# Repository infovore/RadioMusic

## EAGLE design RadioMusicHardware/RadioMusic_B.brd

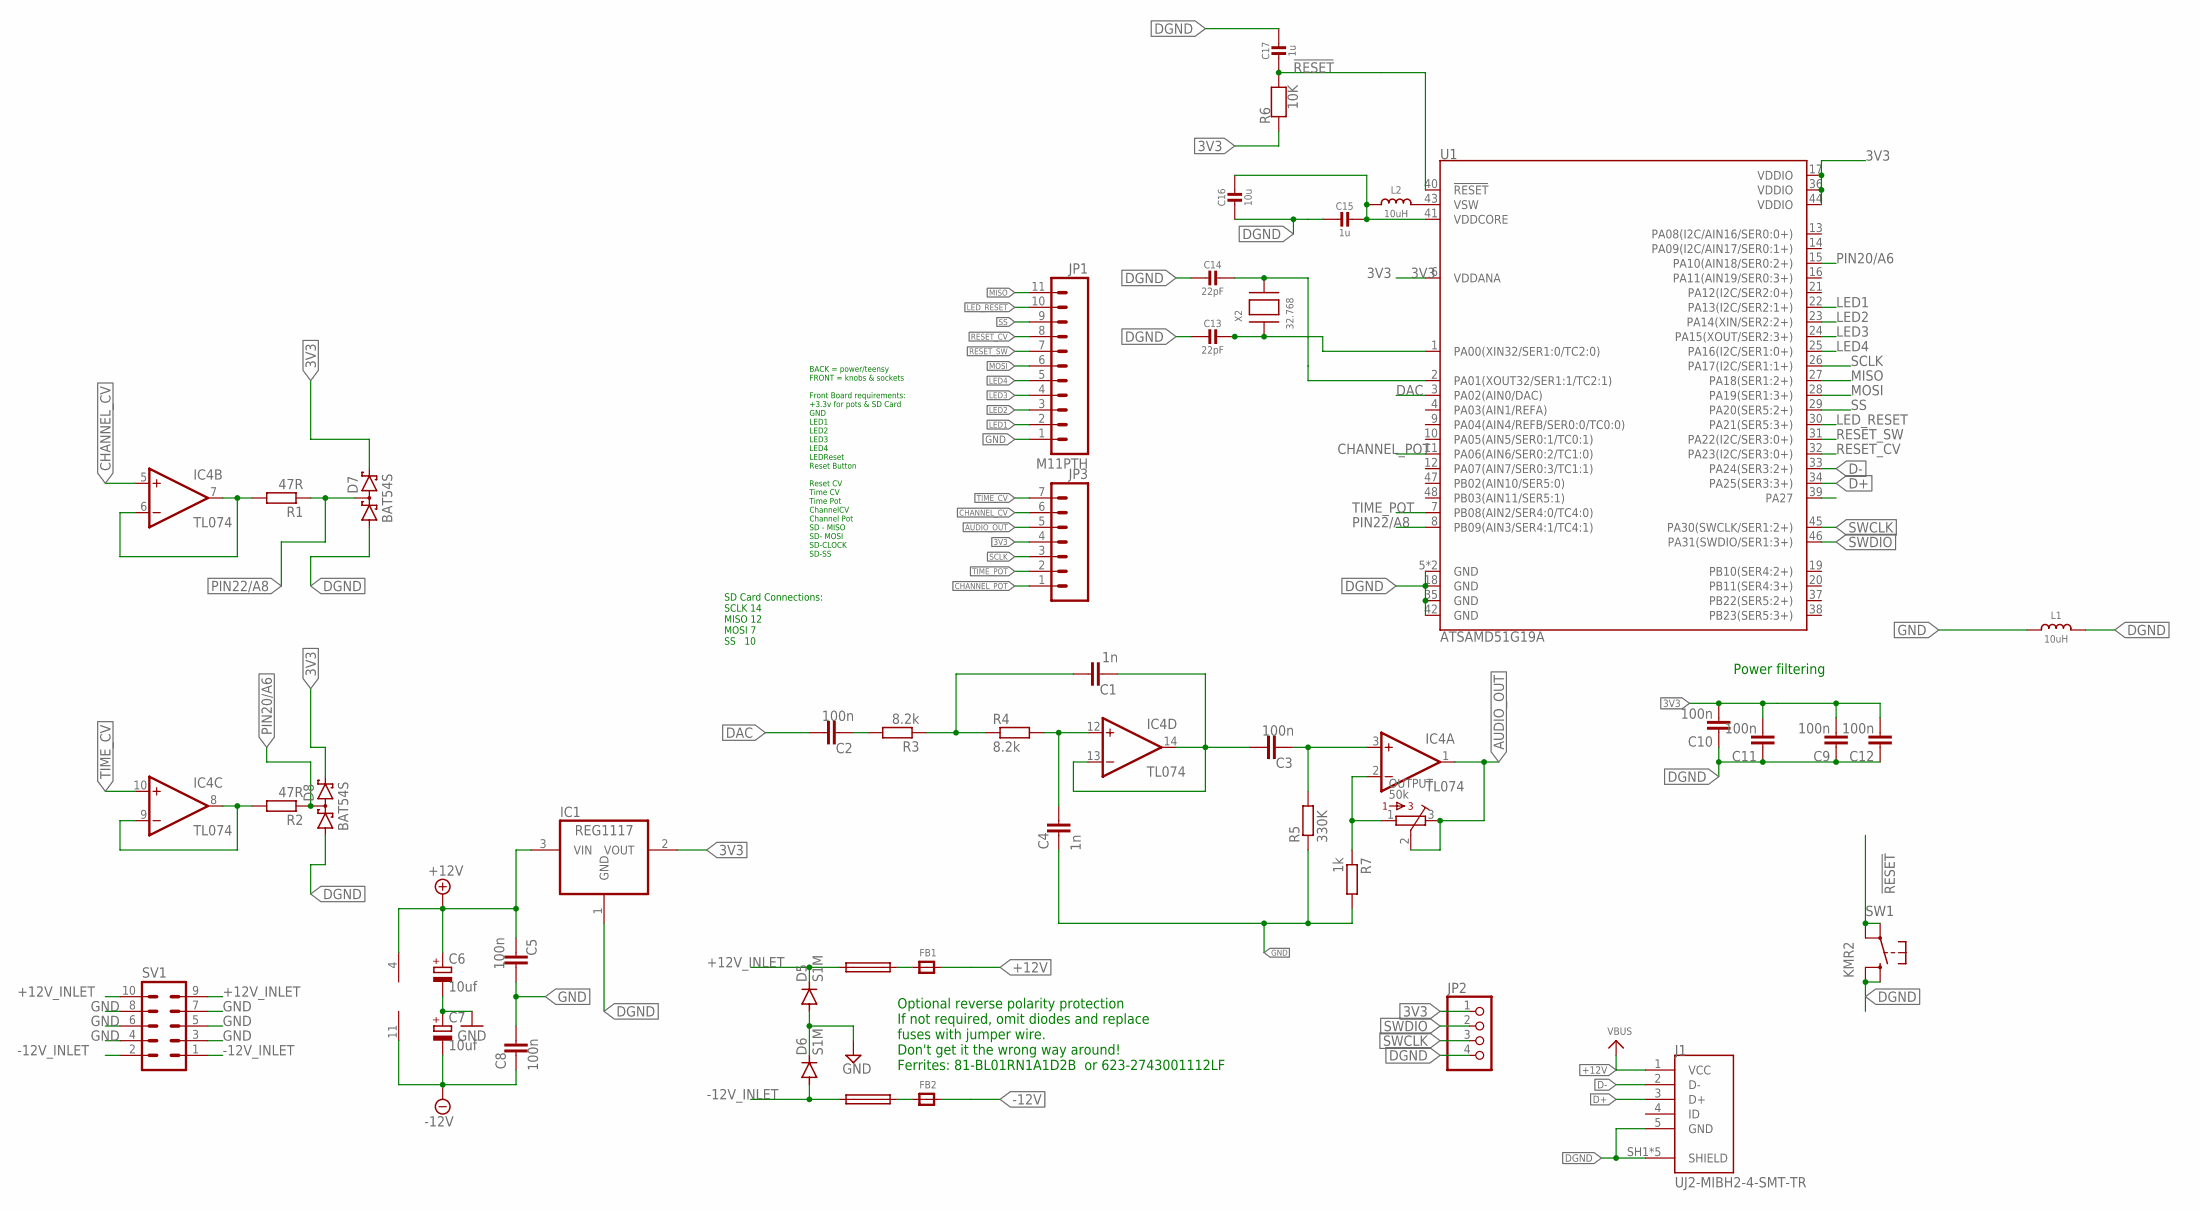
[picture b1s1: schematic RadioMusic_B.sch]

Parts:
C1, C4: 1n; C0603
C2, C3, C5, C8, C9, C10, C11, C12: 100n; C0603
C6, C7: 10uf; PANASONIC_B
C13, C14: 22pF; 0603-NO
C15, C17: 1u; 0603-NO
C16: 10u; 0805-NO
D5, D6: S1M; SMA
D7, D8: BAT54S; SOT23
F1, F2: FUSE; F1206
FB1, FB2: FERRITE_0805; _0805
IC1: REG1117; SOT223
IC4: TL074; SO14
J1: UJ2-MIBH2-4-SMT-TR; CUI_UJ2-MIBH2-4-SMT-TR
JP1: M11PTH; 1X11
JP2: PINHD-1X4; 1X04
JP3: M07; 1X07
L1, L2: 10uH; INDUCTOR_1007
OUTPUT: 50k; 3362P
R1, R2: 47R; R0603
R3, R4: 8.2k; R0603
R5: 330K; R0603
R6: 10K; 0603-NO
R7: 1k; R0603
SV1: 10_PIN_HEADER; MA05-2
SW1: KMR2; BTN_KMR2_4.6X2.8
U1: ATSAMD51G19A; QFN-48
X2: 32.768; XTAL3215

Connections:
3V3: C9.2, C10.2, C11.2, C12.2, C15.1, C16.1, D7.2 (C2), D8.2 (C2), IC1.2 (VOUT), JP2.1, JP3.4, L2.P$1 (1), R6.1, U1.6 (VDDANA), U1.17 (VDDIO), U1.36 (VDDIO), U1.41 (VDDCORE), U1.44 (VDDIO)
!RESET: C17.2, R6.2, SW1.A, SW1.A' (P1), U1.40 (!RESET!)
+12V: C5.2, C6.+, FB1.2, IC1.3 (VIN), IC4.4 (V+), J1.1 (VCC)
+12V_INLET: D5.C, F1.1, SV1.9, SV1.10
-12V: C7.-, C8.2, FB2.2, IC4.11 (V-)
-12V_INLET: D6.A, F2.1, SV1.1, SV1.2
AUDIO_OUT: IC4.1 (OUT), JP3.5, OUTPUT.2, OUTPUT.3
CHANNEL_CV: IC4.5 (+IN), JP3.6
CHANNEL_POT: JP3.1, U1.11 (PA06(AIN6/SER0:2/TC1:0))
D+: J1.3 (D+), U1.34 (PA25(SER3:3+))
D-: J1.2 (D-), U1.33 (PA24(SER3:2+))
DAC: C2.1, U1.3 (PA02(AIN0/DAC))
DGND: C9.1, C10.1, C11.1, C12.1, C13.2, C14.2, C15.2, C16.2, C17.1, D7.1 (A1), D8.1 (A1), IC1.1 (GND), J1.5 (GND), J1.SH1 (SHIELD), J1.SH2 (SHIELD), J1.SH3 (SHIELD), J1.SH4 (SHIELD), J1.SH5 (SHIELD), JP2.4, L1.P$2 (2), SW1.B (S), SW1.B' (S1), U1.5 (GND), U1.18 (GND), U1.35 (GND), U1.42 (GND), U1.EP (GND)
GND: C4.2, C5.1, C6.-, C7.+, C8.1, D5.A, D6.C, JP1.1, L1.P$1 (1), R5.1, R7.2, SV1.3, SV1.4, SV1.5, SV1.6, SV1.7, SV1.8
LED1: JP1.2, U1.22 (PA13(I2C/SER2:1+))
LED2: JP1.3, U1.23 (PA14(XIN/SER2:2+))
LED3: JP1.4, U1.24 (PA15(XOUT/SER2:3+))
LED4: JP1.5, U1.25 (PA16(I2C/SER1:0+))
LED_RESET: JP1.10, U1.30 (PA21(SER5:3+))
MISO: JP1.11, U1.27 (PA18(SER1:2+))
MOSI: JP1.6, U1.28 (PA19(SER1:3+))
unnamed: IC4.8 (OUT), IC4.9 (-IN), R2.2
unnamed: C4.1, IC4.12 (+IN), R4.2
unnamed: IC4.6 (-IN), IC4.7 (OUT), R1.2
unnamed: C1.1, R3.1, R4.1
unnamed: C1.2, C3.1, IC4.13 (-IN), IC4.14 (OUT)
unnamed: C3.2, IC4.3 (+IN), R5.2
unnamed: IC4.2 (-IN), OUTPUT.1, R7.1
unnamed: C13.1, U1.1 (PA00(XIN32/SER1:0/TC2:0)), X2.P$1
unnamed: C14.1, U1.2 (PA01(XOUT32/SER1:1/TC2:1)), X2.P$2
unnamed: C2.2, R3.2
unnamed: L2.P$2 (2), U1.43 (VSW)
unnamed: F1.2, FB1.1
unnamed: F2.2, FB2.1
PIN20/A6: D8.3 (C1A2), R2.1, U1.15 (PA10(AIN18/SER0:2+))
PIN22/A8: D7.3 (C1A2), R1.1, U1.8 (PB09(AIN3/SER4:1/TC4:1))
RESET_CV: JP1.8, U1.32 (PA23(I2C/SER3:0+))
RESET_SW: JP1.7, U1.31 (PA22(I2C/SER3:0+))
SCLK: JP3.3, U1.26 (PA17(I2C/SER1:1+))
SS: JP1.9, U1.29 (PA20(SER5:2+))
SWCLK: JP2.3, U1.45 (PA30(SWCLK/SER1:2+))
SWDIO: JP2.2, U1.46 (PA31(SWDIO/SER1:3+))
TIME_CV: IC4.10 (+IN), JP3.7
TIME_POT: JP3.2, U1.7 (PB08(AIN2/SER4:0/TC4:0))

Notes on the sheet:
Optional reverse polarity protection If not required, omit diodes and replace fuses with jumper wire. Don't get it the wrong way around! Ferrites: 81-BL01RN1A1D2B or 623-2743001112LF
SD Card Connections: SCLK 14 MISO 12 MOSI 7 SS 10
BACK = power/teensy FRONT = knobs & sockets Front Board requirements: +3.3v for pots & SD Card GND LED1 LED2 LED3 LED4 LEDReset Reset Button Reset CV Time CV Time Pot ChannelCV Channel Pot SD - MISO SD- MOSI SD-CLOCK SD-SS
Power filtering

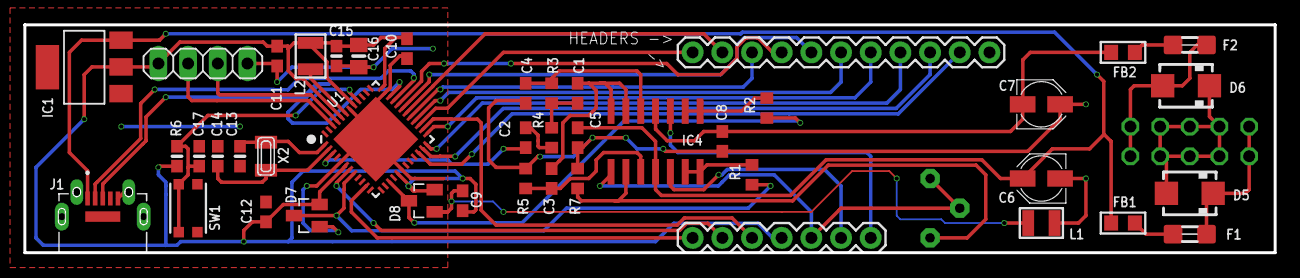
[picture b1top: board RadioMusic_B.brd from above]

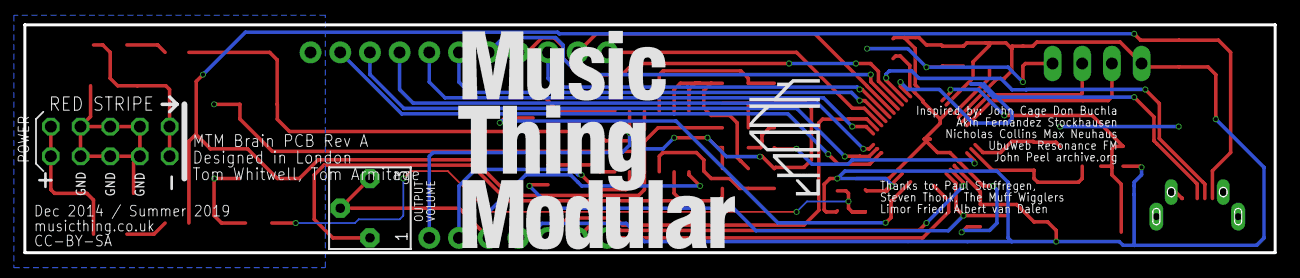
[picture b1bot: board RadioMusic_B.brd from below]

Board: 2 copper layers, 107.0 x 19.5 mm, 47 parts (4 on the bottom side), 44 nets.

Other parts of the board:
U$2: THONK_1CM_SCREENPRINT
U$4: MTM_2CM

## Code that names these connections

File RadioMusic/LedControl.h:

#include <elapsedMillis.h>

#ifndef LedControl_h
#define LedControl_h

/**
 * Chord Organ / Radio Music LED control
 *
 * 4 LEDs across the top and 1 reset LED.
 *
 */
#define LED0 12
#define LED1 11 
#define LED2 10 
#define LED3 9 
#define RESET_LED 13 // Reset LED indicator

class LedControl {

	public:
		LedControl();
		void init();
		void single(int index);
		void multi(uint8_t bits);
		void bankAndSingle(int bank, int index);
		void flash();
		void showReset(boolean high);
	private:
		boolean flashingBank = false;
		elapsedMillis bankFlashTimer = 0;
		uint16_t bankLedFlashTimes[3] = {400,100,30};

};
#endif

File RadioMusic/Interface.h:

#ifndef Interface_h
#define Interface_h

#include "Arduino.h"

#include <Bounce2.h>
#include <elapsedMillis.h>
#include "PlayState.h"
#include "Settings.h"
#include "AnalogInput.h"

#define CHAN_POT_PIN A5 	// pin for Channel pot
#define CHAN_CV_PIN A4 		// pin for Channel CV
#define TIME_POT_PIN A3 	// pin for Time pot
#define TIME_CV_PIN A2 		// pin for Time CV
#define RESET_BUTTON 7 		// Reset button
#define RESET_CV 5 		// Reset pulse input

#define TIME_POT_CHANGED 	1
#define TIME_CV_CHANGED 	1 << 1
#define CHANNEL_CHANGED 	1 << 2
#define CHANGE_START_NOW 	1 << 3
#define BUTTON_SHORT_PRESS 	1 << 4
#define BUTTON_LONG_PRESS 	1 << 5
#define BUTTON_LONG_RELEASE 1 << 6
#define BUTTON_PULSE 		1 << 7
#define RESET_TRIGGERED 	1 << 8
#define ROOT_CV_CHANGED		1 << 9
#define ROOT_POT_CHANGED	1 << 10
#define ROOT_NOTE_CHANGED	1 << 11

#define SHORT_PRESS_DURATION 10
#define LONG_PRESS_DURATION 600
// after LONG_PRESS_DURATION every LONG_PRESS_PULSE_DELAY milliseconds the update
// function will set BUTTON_PULSE
#define LONG_PRESS_PULSE_DELAY 600

#define SAMPLEAVERAGE   16 	// How many values are read and averaged of pot/CV inputs each interface check.

class Interface {
public:
	boolean quantiseRootCV = true;
	boolean quantiseRootPot = true;

	float rootNoteCV = 36;
	float rootNotePot = 36;
	float rootNote = 36;

	boolean buttonHeld = false;
	unsigned long start = 0;

	elapsedMillis buttonHoldTime;

	PlayState* playState;

	Interface() : channelCVInput(CHAN_CV_PIN),
			channelPotInput(CHAN_POT_PIN),
			startCVInput(TIME_CV_PIN),
			startPotInput(TIME_POT_PIN)
	{
		playState = NULL;
	}

	void init(int fileSize, int channels, const Settings& settings, PlayState* state);
	void setChannelCount(uint16_t count);
	void setFileSize(uint32_t fileSize);

	uint16_t update();
	uint16_t updateButton();
private:
	AnalogInput channelCVInput;
	AnalogInput channelPotInput;
	AnalogInput startCVInput;
	AnalogInput startPotInput;

	Bounce resetButtonBounce;
	elapsedMillis buttonTimer = 0;

	uint16_t changes = 0;

	uint16_t startCVDivider = 1;
	boolean channelPotImmediate = true;
	boolean channelCVImmediate = true;
	boolean startPotImmediate = true;
	boolean startCVImmediate = true;

	uint16_t channelCount = 0;
	float rootNoteOld = -100;
	float rootNotePotOld = -100;
	float rootNoteCVOld = -100;

	uint16_t updateChannelControls();
	uint16_t updateStartControls();
	uint16_t updateRootControls();
	boolean pitchMode = false;
};

#endif

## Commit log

2019-05-07 WIP on a SAMD51 back board.
2019-06-03 Rear Board for SAMD51.
2019-06-03 Fixup Firmware for Adafruit boards:
    * use Adafruit Audio library
    * explicitly reference elapsedMillis
    * use FlashStorage fork to replace lack of EEPROM
    * don't use non-existent analog pins
2019-06-03 Notes on SAMD51.
2019-06-04 Tidying silking.
2019-06-04 Ignore vsc.
2019-06-04 Correct pinouts for M4 Express
2019-06-05 Adding SAMD51 notes.
2019-06-05 Connect DGND/GND via inductor. Tidy silking.
2019-08-05 Rev A of MTM Brain board.

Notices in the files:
RadioMusicHardware/RadioMusic_B.brd:
CC-BY-SA
parts and their libraries:
SparkFun-Connectors: Licensing: CC v3.0 Share-Alike You are welcome to use this library for commercial purposes.
SparkFun-IC-Microcontroller: Licensing: Creative Commons ShareAlike 4.0 International - https://creativecommons.org/licenses/by-sa/4.0
